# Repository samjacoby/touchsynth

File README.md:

# Touch Synth
32U4-based Arduino (Leonardo) compatible synthesizer board

In effect, "forked" from bdm.cc

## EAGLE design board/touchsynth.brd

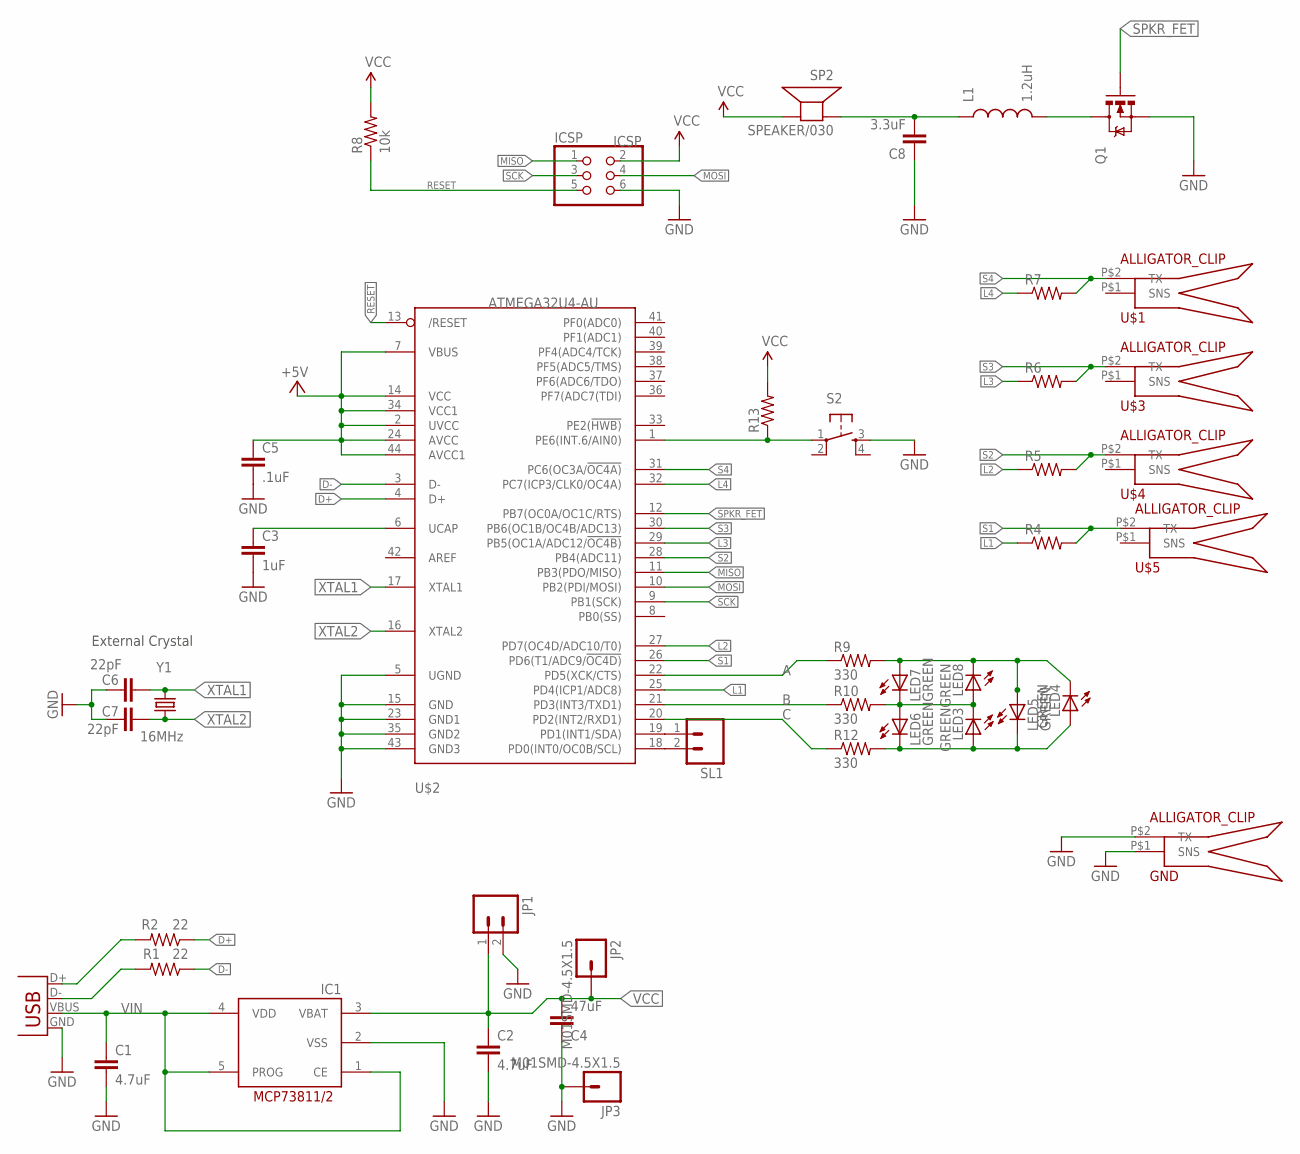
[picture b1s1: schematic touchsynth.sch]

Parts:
C1, C2: 4.7uF; 0603-CAP
C3: 1uF; 0603-CAP
C4: 47uF; 1206
C5: .1uF; 0603-CAP
C6, C7: 22pF; 0402-CAP
C8: 3.3uF; 0603-CAP
GND: ALLIGATOR_CLIP
IC1: MCP73811/2; SOT23-5L
ICSP: ICSP; 2X03
JP1: M02PTH; 1X02
JP2, JP3: M01SMD-4.5X1.5; PAD-1.5X4.5
L1: 1.2uH; 1210
LED3, LED4, LED5, LED6, LED7, LED8: GREEN; LED-1206-BOTTOM
Q1: MOSFET-NCHANNELSMD; SOT23-3
R1, R2: 22; 0402-RES
R4, R5, R6, R7, R13: RESISTOR0603-RES; 0603-RES
R8: 10k; 0603-RES
R9, R10, R12: 330; 0603-RES
S2: TAC_SWITCHSMD; TACTILE_SWITCH_SMD
SL1: M02; 02P
SP2: SPEAKER/030; AST-030
U$1, U$3, U$4, U$5: ALLIGATOR_CLIP
U$2: ATMEGA32U4-AU; TQFP44-THIN
X1: USB; USB-MINIB-NOSTOP-THIN
Y1: 16MHz; CRYSTAL-SMD-5X3

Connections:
A: R9.1, U$2.22 (PD5(XCK/CTS))
B: R10.1, U$2.21 (PD3(INT3/TXD1))
C: R12.1, U$2.20 (PD2(INT2/RXD1))
D+: R2.1, U$2.4 (D+)
D-: R1.1, U$2.3 (D-)
GND: C1.2, C2.2, C3.2, C4.1, C5.2, C6.2, C7.2, C8.1, GND.P$1 (SNS), GND.P$2 (TX), IC1.2 (VSS), ICSP.6, JP1.2, JP3.P$1, Q1.2 (S), S2.3, U$2.5 (UGND), U$2.15 (GND), U$2.23 (GND1), U$2.35 (GND2), U$2.43 (GND3), X1.GND
L1: R4.1, U$2.25 (PD4(ICP1/ADC8))
L2: R5.1, U$2.27 (PD7(OC4D/ADC10/T0))
L3: R6.1, U$2.29 (PB5(OC1A/ADC12/!OC4B))
L4: R7.1, U$2.32 (PC7(ICP3/CLK0/OC4A))
MISO: ICSP.1, U$2.11 (PB3(PDO/MISO))
MOSI: ICSP.4, U$2.10 (PB2(PDI/MOSI))
unnamed: C3.1, U$2.6 (UCAP)
unnamed: C8.2, L1.1, SP2.1 (+)
unnamed: SL1.1, U$2.19 (PD1(INT1/SDA))
unnamed: R13.1, S2.1, U$2.1 (PE6(INT.6/AIN0))
unnamed: LED3.C, LED6.A, LED7.C, LED8.A, R10.2
unnamed: R1.2, X1.D-
unnamed: SL1.2, U$2.18 (PD0(INT0/OC0B/SCL))
unnamed: R2.2, X1.D+
unnamed: LED4.C, LED5.A, LED7.A, LED8.C, R9.2
unnamed: LED3.A, LED4.A, LED5.C, LED6.C, R12.2
unnamed: L1.2, Q1.3 (D)
RESET: ICSP.5, R8.1, U$2.13 (/RESET)
S1: R4.2, U$2.26 (PD6(T1/ADC9/!OC4D)), U$5.P$2 (TX)
S2: R5.2, U$2.28 (PB4(ADC11)), U$4.P$2 (TX)
S3: R6.2, U$2.30 (PB6(OC1B/OC4B/ADC13)), U$3.P$2 (TX)
S4: R7.2, U$1.P$2 (TX), U$2.31 (PC6(OC3A/!OC4A))
SCK: ICSP.3, U$2.9 (PB1(SCK))
SPKR_FET: Q1.1 (G), U$2.12 (PB7(OC0A/OC1C/RTS))
VCC: C2.1, C4.2, C5.1, IC1.3 (VBAT), ICSP.2, JP1.1, JP2.P$1, R8.2, R13.2, SP2.2 (-), U$2.2 (UVCC), U$2.7 (VBUS), U$2.14 (VCC), U$2.24 (AVCC), U$2.34 (VCC1), U$2.44 (AVCC1)
VIN: C1.1, IC1.1 (CE), IC1.4 (VDD), IC1.5 (PROG), X1.VBUS
XTAL1: C6.1, U$2.17 (XTAL1), Y1.3 (2)
XTAL2: C7.1, U$2.16 (XTAL2), Y1.1

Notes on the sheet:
External Crystal

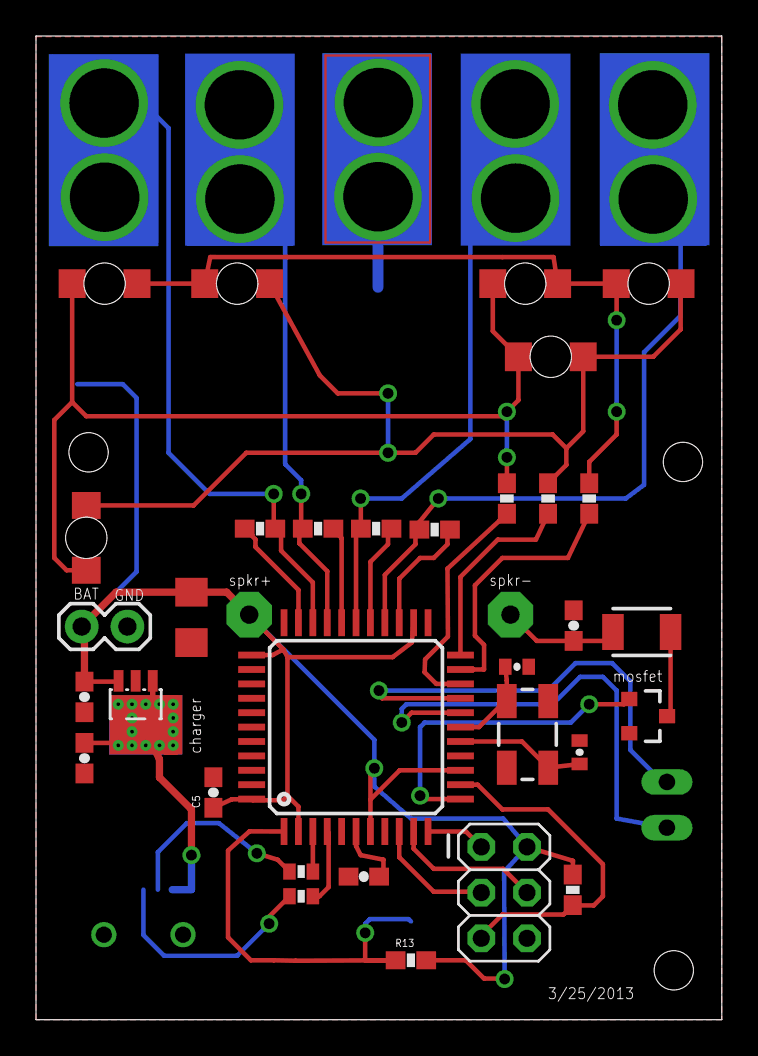
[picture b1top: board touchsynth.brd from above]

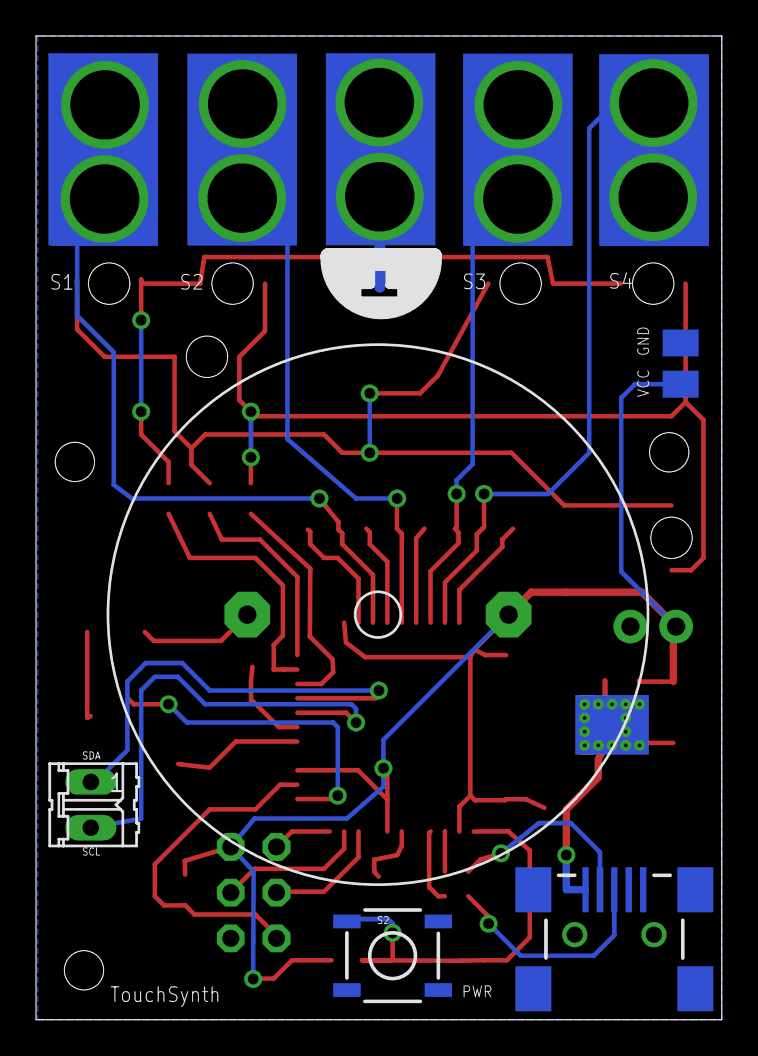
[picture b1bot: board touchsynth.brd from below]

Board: 2 copper layers, 38.1 x 54.7 mm, 43 parts (10 on the bottom side), 34 nets.

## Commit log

2013-01-17 What is going on?
2013-01-17 Working. This sucker is working alright.
2013-01-19 Generate a sinewave and header files.
2013-01-19 Limping along.
2013-01-20 Starting to add audio generation.
2013-01-21 Changed to cpp to resolve linking issues.
2013-01-21 adding some sound generation
2013-01-21 track this.
2013-01-21 Shifting note definition to main.
2013-01-21 Checking in on touch_timer_sound.
2013-01-22 This is looking good. Timer1 & Timer3 running.
2013-01-22 Adding after name change, along with new header file.
2013-01-22 Working FM sound, running through synth.
2013-01-22 Working.
2013-01-22 This is working PCM, but no FM going on.
2013-01-22 And we've got a little song.
2013-01-22 Working FM, I think.
2013-01-22 Working with capacitive sensor.
2013-01-23 Working, with modulation and what-not.
2013-01-23 Trying to get something a little nicer outt've this.
2013-01-24 Playing discrete notes, now, for whatever reason.
2013-01-24 Keep track of certain things, as the master does.
2013-01-24 Sensor stuff should go in sense.c & sense.h
2013-01-26 Fix volume adjustment.
2013-03-07 Finally, getting something workable.
2013-03-15 Latest + filename change.
2013-03-15 Adding readme.
2013-03-16 Language.
2013-03-16 Lose these.
2013-03-19 Latest and greatest.
2013-03-20 Starting to add button functionality.
2013-03-22 Bad news.
2013-03-22 Adding LED files.
2013-03-23 Working sound, Working LEDs.
2013-03-24 Working button.
2013-03-24 Something is strange, but works.
2013-03-25 Keep track of the boards in here.
2013-03-29 Checking in, just because I break this sucker so often.
2013-03-29 Mostly working.
2013-04-11 Fixing LEDs.
2013-04-11 Checking in, prior to adding new channels.
2013-04-11 Polyphonyopen touchsynth.ino A very quiet polyphony.

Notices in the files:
parts and their libraries:
SparkFun-LED: Licensing: CC v3.0 Share-Alike You are welcome to use this library for commercial purposes.
